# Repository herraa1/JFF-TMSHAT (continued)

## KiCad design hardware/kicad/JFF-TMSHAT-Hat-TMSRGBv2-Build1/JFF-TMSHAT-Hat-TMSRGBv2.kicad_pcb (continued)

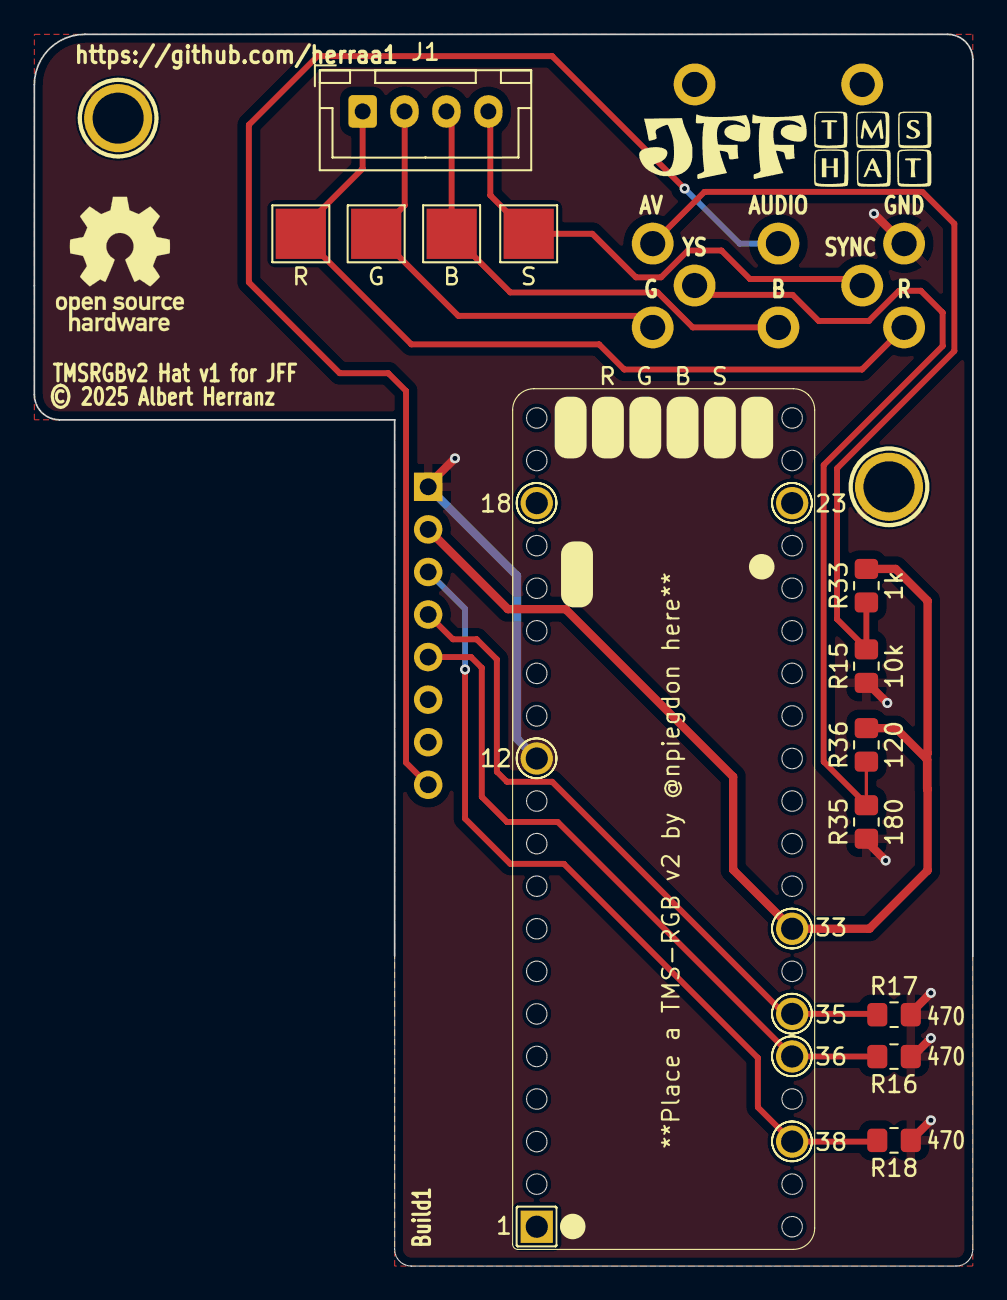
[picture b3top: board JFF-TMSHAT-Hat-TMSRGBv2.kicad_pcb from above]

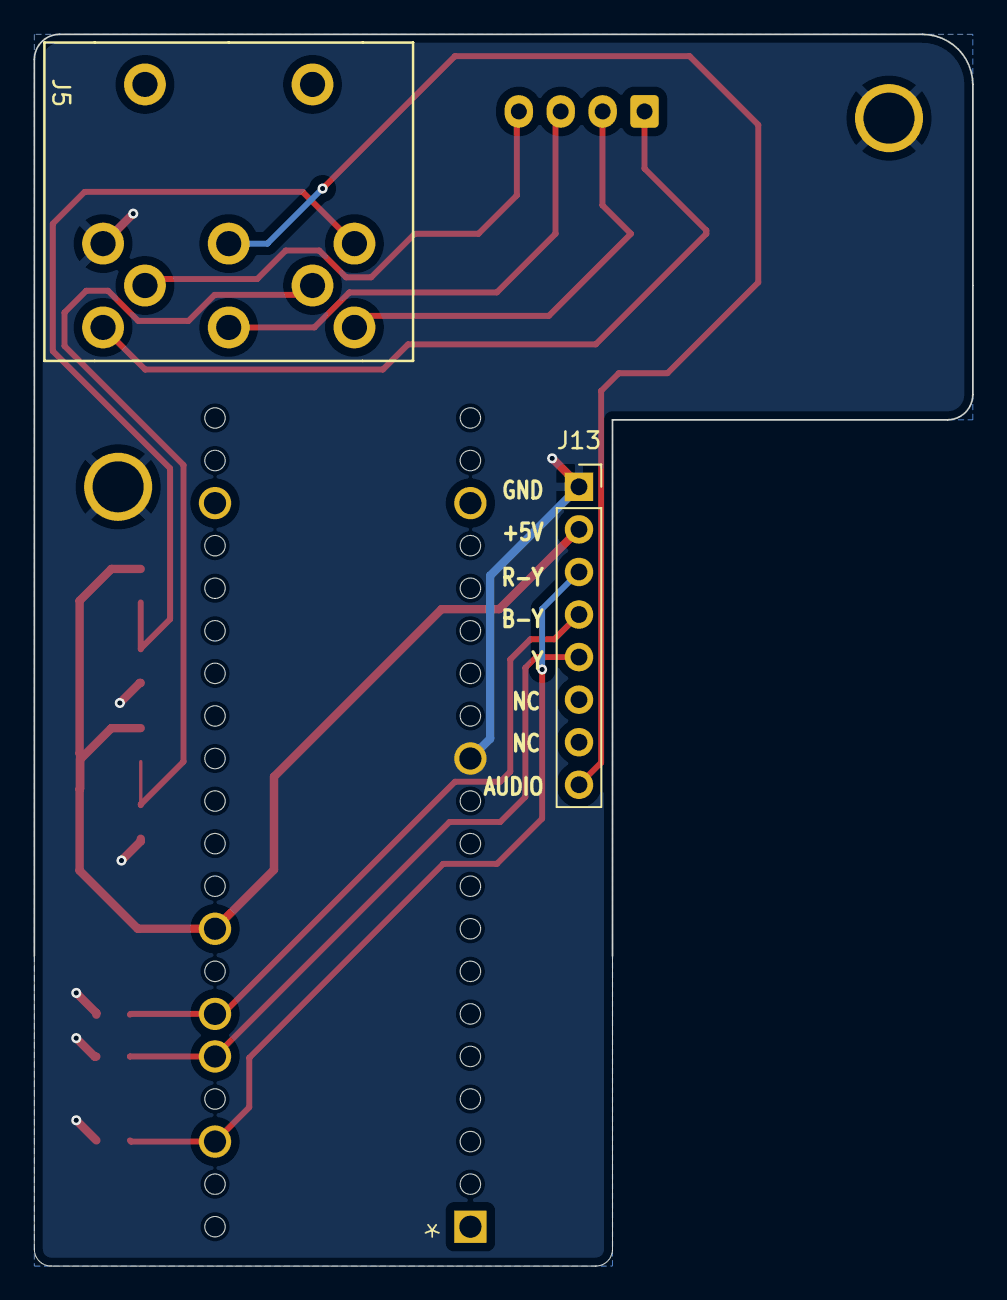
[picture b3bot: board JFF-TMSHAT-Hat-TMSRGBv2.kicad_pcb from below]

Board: 2 copper layers, 56.0 x 73.5 mm, 18 parts (3 on the bottom side), 12 nets.

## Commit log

2025-07-22 initial commit.
2025-07-22 readme: fix image link for modified mainboard
2025-07-22 readme: added kicanvas links
2025-07-22 readme: add link to DIN8 A/V connector and clarify some text
2025-07-23 readme: minor fixes, clarifications, considerations and notes
2025-07-25 tmshats: add missing Y,R-Y,B-Y resistors
2025-07-25 tmshats: update iboms and renders
2025-07-26 tmshats: re-routed for enhanced reference plane
2025-07-27 tmshats: changed logos, minor routing change
2025-07-27 tmshats: add back missing YS silkscreen text
2025-08-20 readme: update progress on mainboard
2025-09-11 readme: update status, mainboard and tmsrgbcustom hat working
2025-09-11 readme: add build1 images
2025-09-11 readme: speed up page loading using low res images
2025-09-11 readme: add picture of TMS9929 50Hz test with tmsrgbcustom hat
2025-09-11 readme: be more precise for revision names
2025-09-12 readme: more revision names, enhance J13 signal table description
2025-09-12 readme: add sponsorship section and enhance information for built boards
2025-09-12 readme: try check mark emojis
2025-09-21 readme: add project logo
2025-09-24 readme: tested TMSRGBCustom with TMS9928AN
2025-10-03 readme: jff-joy-fix has been validated and works fine
2025-10-04 readme: add link to JFF-1.1-joyfix-board-v1
2025-10-06 add new revision 1.1c-TMSHAT equivalent to 1.1c fixing the joystick circuit bug
2025-10-06 readme: minor revision clarifications
2025-10-06 readme: additional revision clarification
2025-10-07 kicad: update rev number and dates for 1.1c-TMSHAT
2025-10-11 TMSRGBv2 TMSHAT built and tested successfully
2025-10-19 readme: mark project as complete
2025-11-18 readme: pending test completed successfully
